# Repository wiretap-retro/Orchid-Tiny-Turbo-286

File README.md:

# Orchid Tiny Turbo 286
A clone of the Orchid Tiny Turbo 286 acclerator to upgrade an XT system. Based on schematics by Tube Time.

## Info / Warning
Build at your own risk This design is unconfirmed. PAL dumps have been added, courtesy of tomatolicious on the Retro Dreams and Techy Things Discord group. I do not have the original board, so this is a rough layout, not exactly the same size since it uses socketed footprints. However, it does abide by the ISA standard height (121.92mm) and uses a readily available slot cover that would need to be drilled for the switch to fit through. Board may require some more work -- this is considered a non-functional alpha release.
\
\
Built per the schematics from Tube Time's github found here: https://github.com/schlae/tiny-turbo-286

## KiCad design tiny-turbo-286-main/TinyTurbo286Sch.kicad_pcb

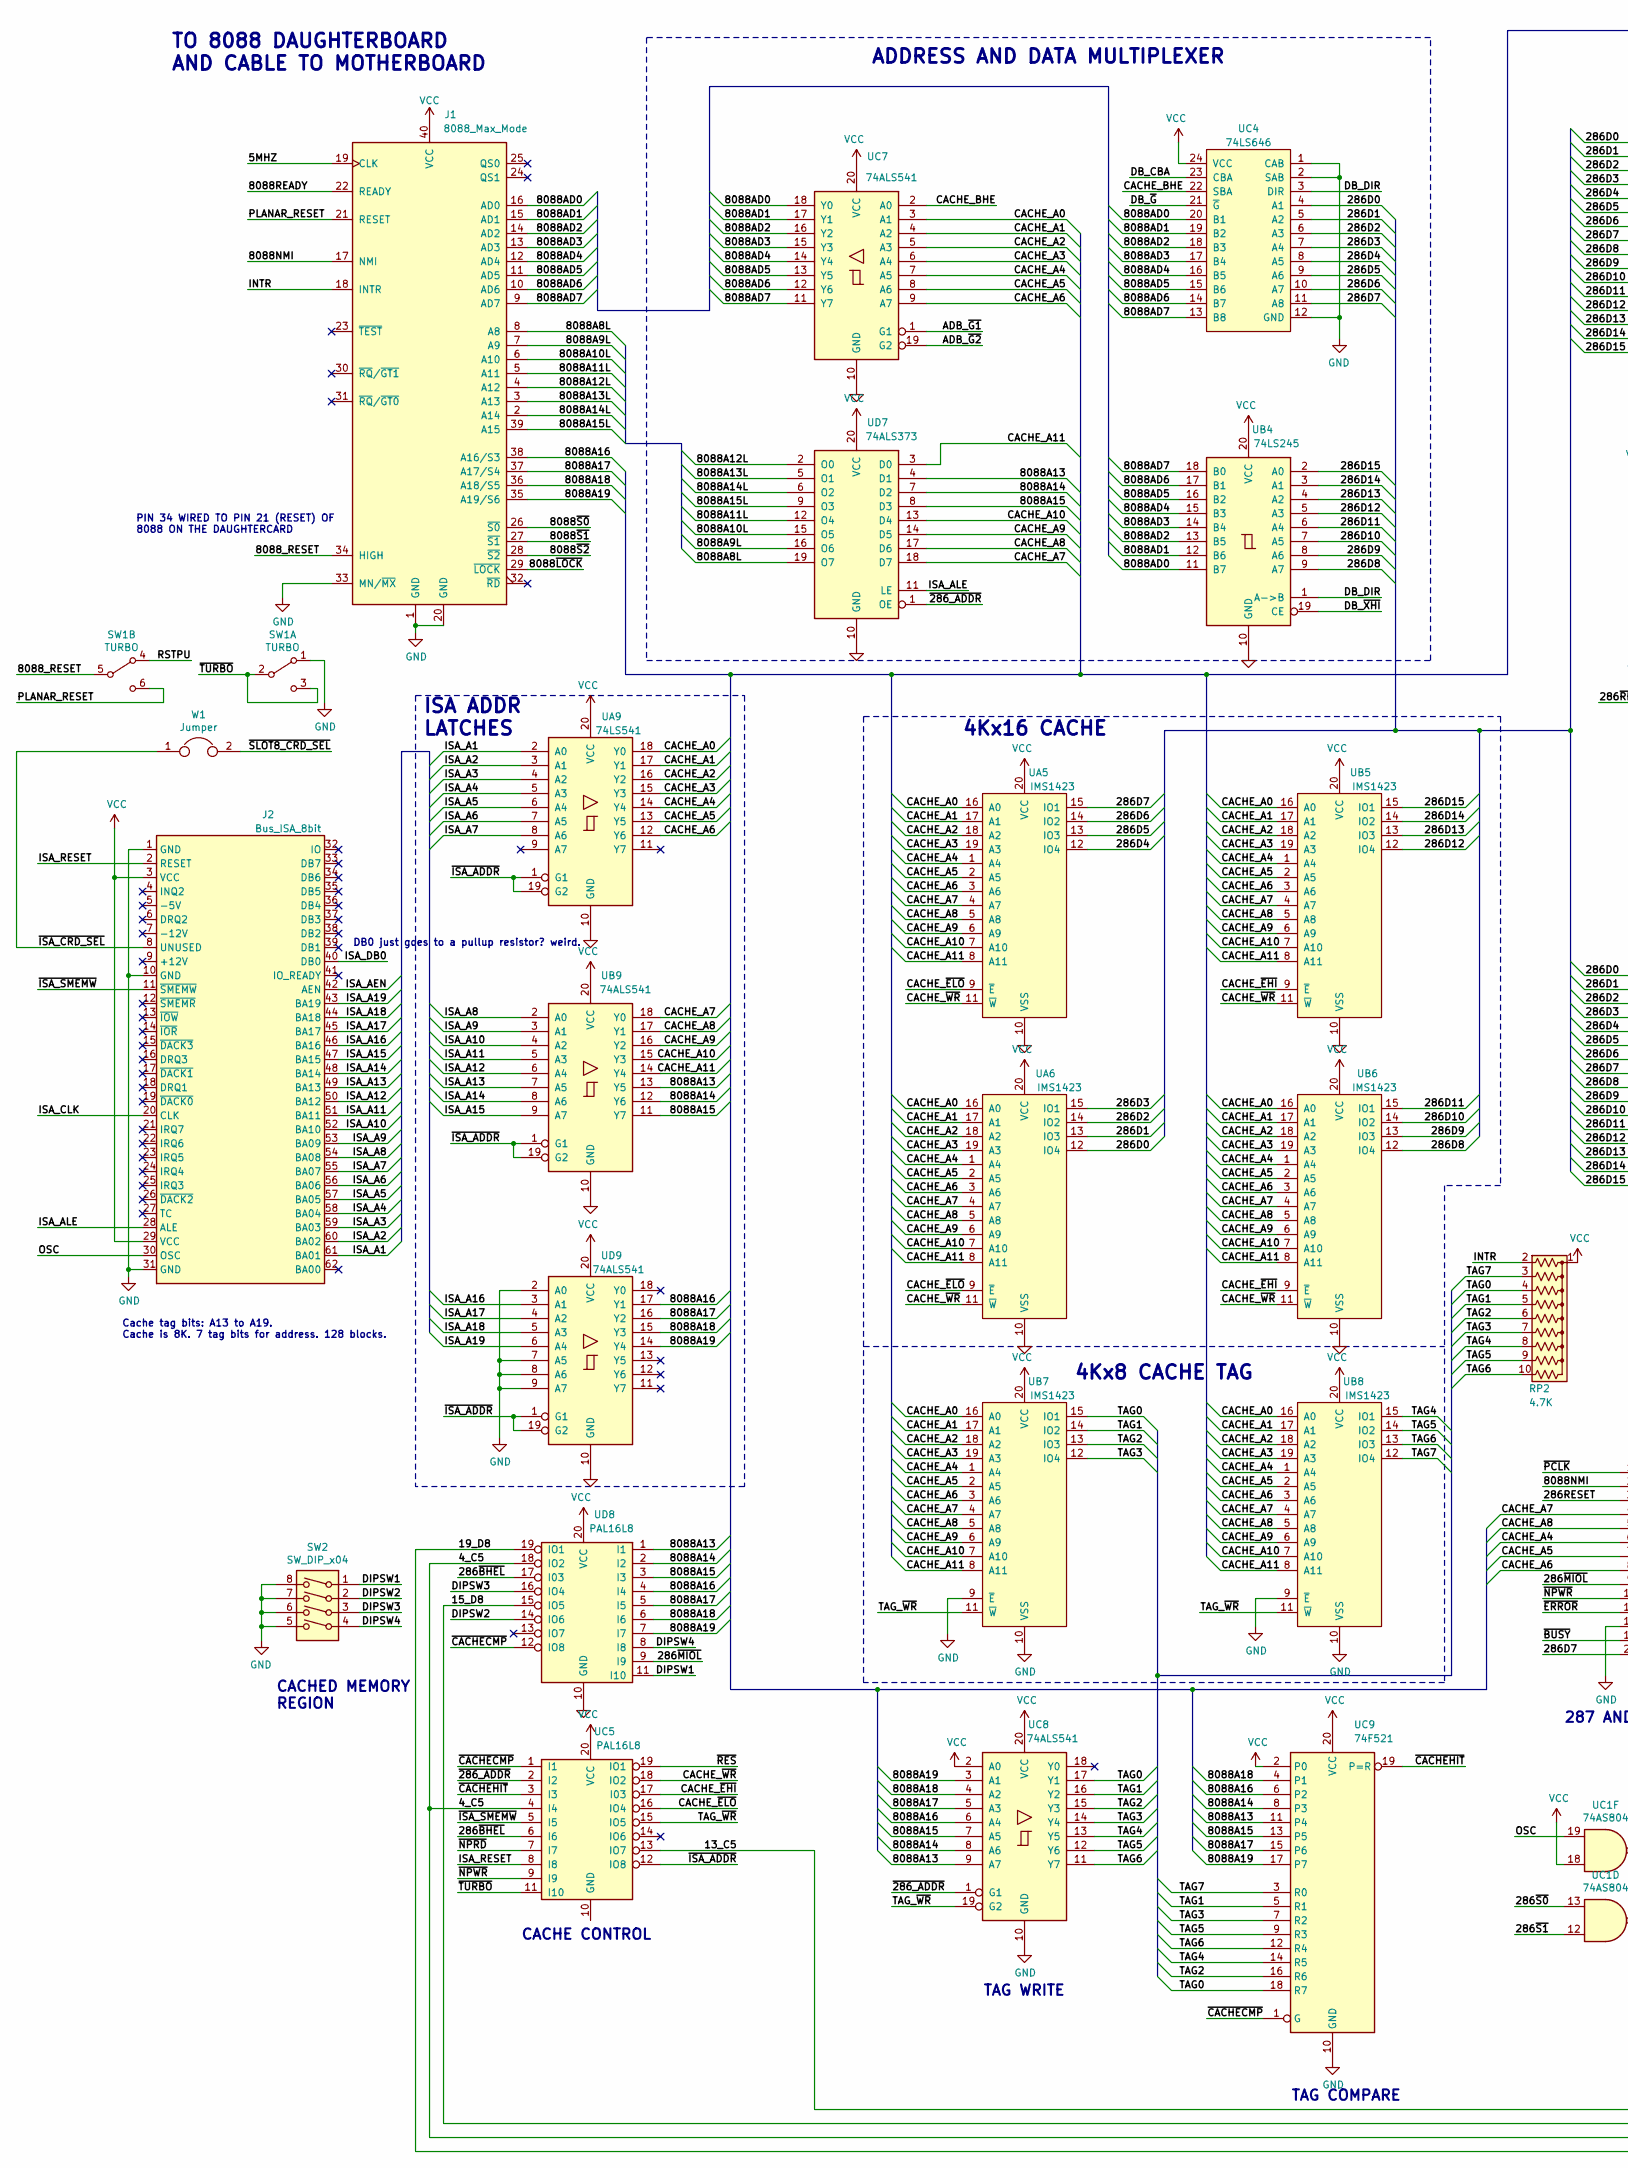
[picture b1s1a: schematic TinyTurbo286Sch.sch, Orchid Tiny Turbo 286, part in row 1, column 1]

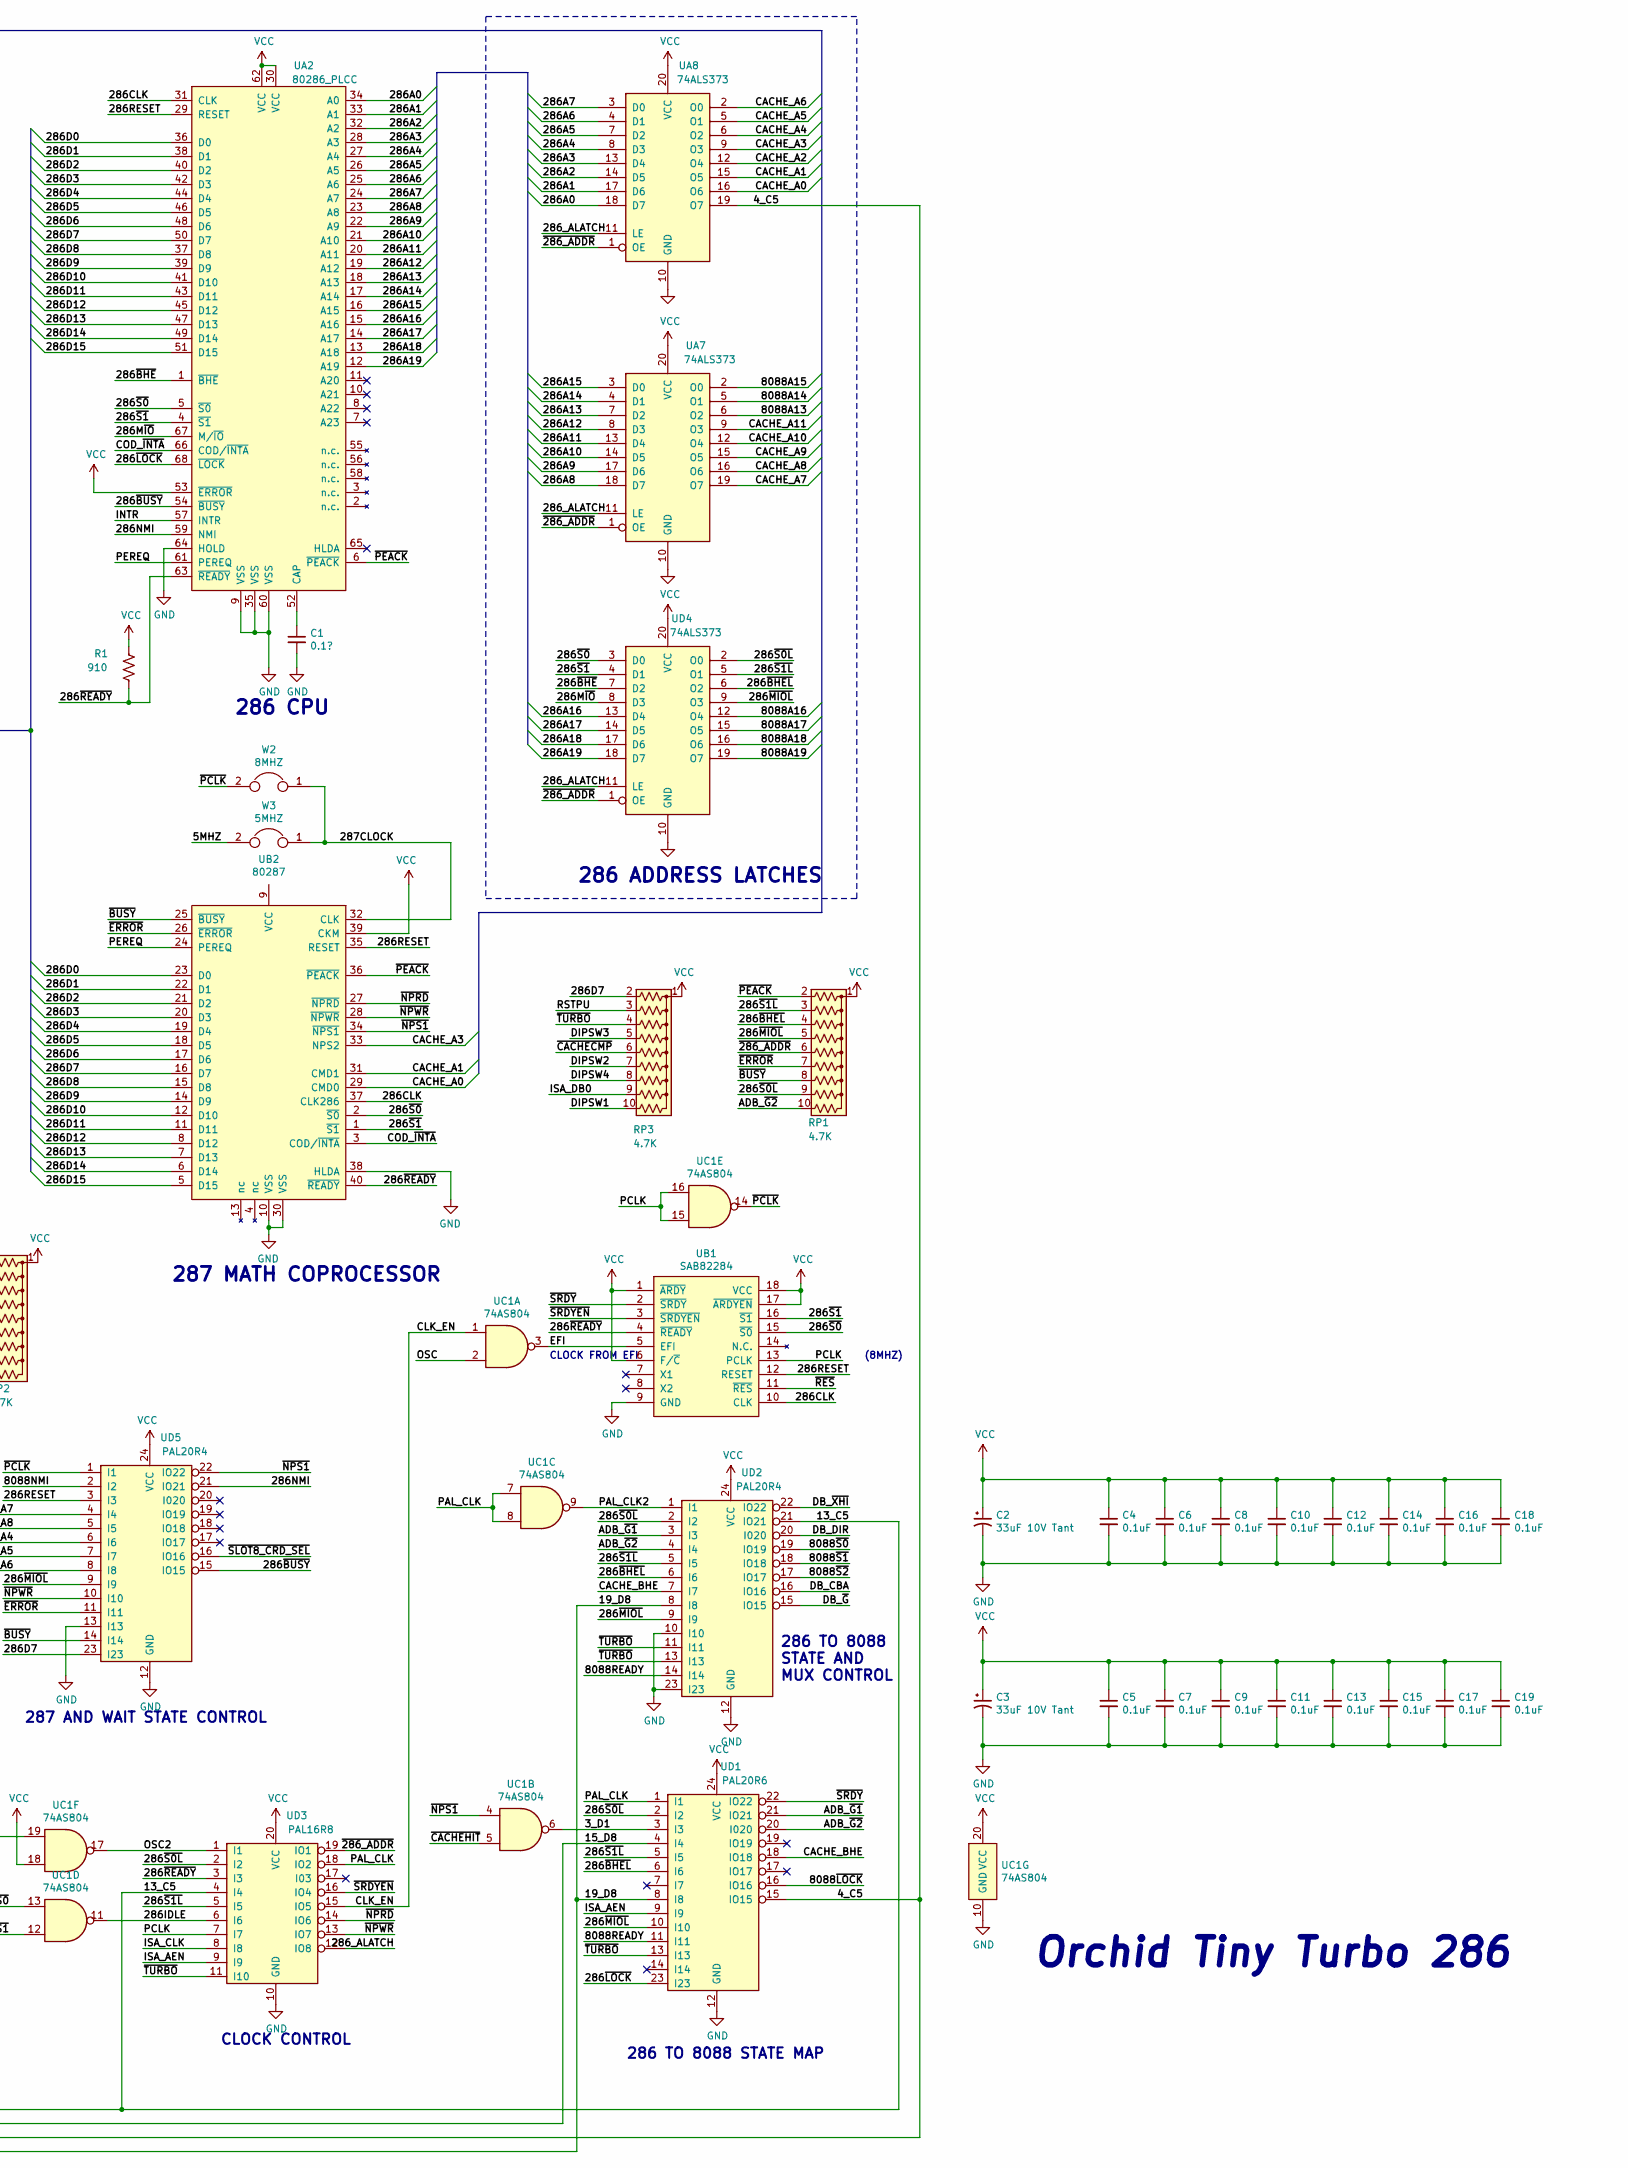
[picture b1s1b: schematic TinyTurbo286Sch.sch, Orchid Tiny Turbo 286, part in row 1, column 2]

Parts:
C1: 0.1?; C320C104J3G5TA
C2, C3: 33uF 10V Tant; CP_Radial_Tantal_D6.0mm_P5.00mm
C4, C5, C6, C7, C8, C9, C10, C11, C12, C13, C14, C15, C16, C17, C18, C19: 0.1uF; C320C104J3G5TA
J1: 8088_Max_Mode; PinSocket_2x20_P2.54mm_Vertical
J2: Bus_ISA_8bit; BUS_XT
R1: 910; R_Axial_DIN0207_L6.3mm_D2.5mm_P7.62mm_Horizontal
RP1, RP2, RP3: 4.7K; R_Array_SIP10
SW1: TURBO; A201MD9AQ04
SW2: SW_DIP_x04; DIP810W60P254L1209H480Q8N
UA2: 80286_PLCC; PLCC-68_THT-Socket
UA5, UA6: IMS1423; DIP-20_W7.62mm_Socket
UA7, UA8: 74ALS373; DIP-20_W7.62mm_Socket
UA9: 74LS541; DIP-20_W7.62mm_Socket
UB1: SAB82284; DIP-18_W7.62mm_Socket
UB2: 80287; DIP-40_W15.24mm_Socket
UB4: 74LS245; DIP-20_W7.62mm_Socket
UB5, UB6, UB7, UB8: IMS1423; DIP-20_W7.62mm_Socket
UB9: 74ALS541; DIP-20_W7.62mm_Socket
UC1: 74AS804; DIP-20_W7.62mm_Socket
UC4: 74LS646; DIP-24_W7.62mm_Socket
UC5: PAL16L8; DIP-20_W7.62mm_Socket
UC7, UC8: 74ALS541; DIP-20_W7.62mm_Socket
UC9: 74F521; DIP-20_W7.62mm_Socket
UD1: PAL20R6; DIP-24_W7.62mm_Socket
UD2, UD5: PAL20R4; DIP-24_W7.62mm_Socket
UD3: PAL16R8; DIP-20_W7.62mm_Socket
UD4, UD7: 74ALS373; DIP-20_W7.62mm_Socket
UD8: PAL16L8; DIP-20_W7.62mm_Socket
UD9: 74ALS541; DIP-20_W7.62mm_Socket
W1: Jumper; PinHeader_1x02_P2.54mm_Vertical
W2: 8MHZ; PinHeader_1x02_P2.54mm_Vertical
W3: 5MHZ; PinHeader_1x02_P2.54mm_Vertical

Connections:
/3_D1: UC1.6, UD1.3 (I3)
/4_C5: UA8.19 (O7), UC5.4 (I4), UD1.15 (IO15), UD8.18 (IO2)
/5MHZ: J1.19 (CLK), W3.2
/13_C5: UC5.13 (IO7), UD2.21 (IO21), UD3.4 (I4)
/15_D8: UD1.4 (I4), UD8.15 (IO5)
/19_D8: UD1.8 (I8), UD2.8 (I8), UD8.19 (IO1)
/286A0: UA2.34 (A0), UA8.18 (D7)
/286A1: UA2.33 (A1), UA8.17 (D6)
/286A2: UA2.32 (A2), UA8.14 (D5)
/286A3: UA2.28 (A3), UA8.13 (D4)
/286A4: UA2.27 (A4), UA8.8 (D3)
/286A5: UA2.26 (A5), UA8.7 (D2)
/286A6: UA2.25 (A6), UA8.4 (D1)
/286A7: UA2.24 (A7), UA8.3 (D0)
/286A8: UA2.23 (A8), UA7.18 (D7)
/286A9: UA2.22 (A9), UA7.17 (D6)
/286A10: UA2.21 (A10), UA7.14 (D5)
/286A11: UA2.20 (A11), UA7.13 (D4)
/286A12: UA2.19 (A12), UA7.8 (D3)
/286A13: UA2.18 (A13), UA7.7 (D2)
/286A14: UA2.17 (A14), UA7.4 (D1)
/286A15: UA2.16 (A15), UA7.3 (D0)
/286A16: UA2.15 (A16), UD4.13 (D4)
/286A17: UA2.14 (A17), UD4.14 (D5)
/286A18: UA2.13 (A18), UD4.17 (D6)
/286A19: UA2.12 (A19), UD4.18 (D7)
/286CLK: UA2.31 (CLK), UB1.10 (CLK), UB2.37 (CLK286)
/286D0: UA2.36 (D0), UA6.12 (IO4), UB2.23 (D0), UC4.4 (A1)
/286D1: UA2.38 (D1), UA6.13 (IO3), UB2.22 (D1), UC4.5 (A2)
/286D2: UA2.40 (D2), UA6.14 (IO2), UB2.21 (D2), UC4.6 (A3)
/286D3: UA2.42 (D3), UA6.15 (IO1), UB2.20 (D3), UC4.7 (A4)
/286D4: UA2.44 (D4), UA5.12 (IO4), UB2.19 (D4), UC4.8 (A5)
/286D5: UA2.46 (D5), UA5.13 (IO3), UB2.18 (D5), UC4.9 (A6)
/286D6: UA2.48 (D6), UA5.14 (IO2), UB2.17 (D6), UC4.10 (A7)
/286D7: RP3.2 (R1), UA2.50 (D7), UA5.15 (IO1), UB2.16 (D7), UC4.11 (A8), UD5.23 (I23)
/286D8: UA2.37 (D8), UB2.15 (D8), UB4.9 (A7), UB6.12 (IO4)
/286D9: UA2.39 (D9), UB2.14 (D9), UB4.8 (A6), UB6.13 (IO3)
/286D10: UA2.41 (D10), UB2.12 (D10), UB4.7 (A5), UB6.14 (IO2)
/286D11: UA2.43 (D11), UB2.11 (D11), UB4.6 (A4), UB6.15 (IO1)
/286D12: UA2.45 (D12), UB2.8 (D12), UB4.5 (A3), UB5.12 (IO4)
/286D13: UA2.47 (D13), UB2.7 (D13), UB4.4 (A2), UB5.13 (IO3)
/286D14: UA2.49 (D14), UB2.6 (D14), UB4.3 (A1), UB5.14 (IO2)
/286D15: UA2.51 (D15), UB2.5 (D15), UB4.2 (A0), UB5.15 (IO1)
/286IDLE: UC1.11, UD3.6 (I6)
/286M~IO: UA2.67 (M/~IO), UD4.8 (D3)
/286NMI: UA2.59 (NMI), UD5.21 (IO21)
/286RESET: UA2.29 (RESET), UB1.12 (RESET), UB2.35 (RESET), UD5.3 (I3)
/286_ALATCH: UA7.11 (LE), UA8.11 (LE), UD3.12 (IO8), UD4.11 (LE)
/286~BHE: UA2.1 (~BHE), UD4.7 (D2)
/286~BHEL: RP1.4 (R3), UC5.6 (I6), UD1.6 (I6), UD2.6 (I6), UD4.6 (O2), UD8.17 (I03)
/286~BUSY: UA2.54 (~BUSY), UD5.15 (IO15)
/286~LOCK: UA2.68 (~LOCK), UD1.23 (I23)
/286~MIOL: RP1.5 (R4), UD1.10 (I10), UD2.9 (I9), UD4.9 (O3), UD5.9 (I9), UD8.9 (I9)
/286~READY: R1.2, UA2.63 (~READY), UB1.4 (~READY), UB2.40 (~READY), UD3.3 (I3)
/286~S0: UA2.5 (~S0), UB1.15 (~S0), UB2.2 (~S0), UC1.13, UD4.3 (D0)
/286~S0L: RP1.9 (R8), UD1.2 (I2), UD2.2 (I2), UD3.2 (I2), UD4.2 (O0)
/286~S1: UA2.4 (~S1), UB1.16 (~S1), UB2.1 (~S1), UC1.12, UD4.4 (D1)
/286~S1L: RP1.3 (R2), UD1.5 (I5), UD2.5 (I5), UD3.5 (I5), UD4.5 (O1)
/287CLOCK: UB2.32 (CLK), W2.1, W3.1
/8088A8L: J1.8 (A8), UD7.19 (O7)
/8088A9L: J1.7 (A9), UD7.16 (O6)
/8088A10L: J1.6 (A10), UD7.15 (O5)
/8088A11L: J1.5 (A11), UD7.12 (O4)
/8088A12L: J1.4 (A12), UD7.2 (O0)
/8088A13: UA7.6 (O2), UB9.13 (Y5), UC8.9 (A7), UC9.11 (P4), UD7.4 (D1), UD8.1 (I1)
/8088A13L: J1.3 (A13), UD7.5 (O1)
/8088A14: UA7.5 (O1), UB9.12 (Y6), UC8.8 (A6), UC9.8 (P3), UD7.7 (D2), UD8.2 (I2)
/8088A14L: J1.2 (A14), UD7.6 (O2)
/8088A15: UA7.2 (O0), UB9.11 (Y7), UC8.7 (A5), UC9.13 (P5), UD7.8 (D3), UD8.3 (I3)
/8088A15L: J1.39 (A15), UD7.9 (O3)
/8088A16: J1.38 (A16/S3), UC8.6 (A4), UC9.6 (P2), UD4.12 (O4), UD8.4 (I4), UD9.17 (Y1)
/8088A17: J1.37 (A17/S4), UC8.5 (A3), UC9.15 (P6), UD4.15 (O5), UD8.5 (I5), UD9.16 (Y2)
/8088A18: J1.36 (A18/S5), UC8.4 (A2), UC9.4 (P1), UD4.16 (O6), UD8.6 (I6), UD9.15 (Y3)
/8088A19: J1.35 (A19/S6), UC8.3 (A1), UC9.17 (P7), UD4.19 (O7), UD8.7 (I7), UD9.14 (Y4)
/8088AD0: J1.16 (AD0), UB4.11 (B7), UC4.20 (B1), UC7.18 (Y0)
/8088AD1: J1.15 (AD1), UB4.12 (B6), UC4.19 (B2), UC7.17 (Y1)
/8088AD2: J1.14 (AD2), UB4.13 (B5), UC4.18 (B3), UC7.16 (Y2)
/8088AD3: J1.13 (AD3), UB4.14 (B4), UC4.17 (B4), UC7.15 (Y3)
/8088AD4: J1.12 (AD4), UB4.15 (B3), UC4.16 (B5), UC7.14 (Y4)
/8088AD5: J1.11 (AD5), UB4.16 (B2), UC4.15 (B6), UC7.13 (Y5)
/8088AD6: J1.10 (AD6), UB4.17 (B1), UC4.14 (B7), UC7.12 (Y6)
/8088AD7: J1.9 (AD7), UB4.18 (B0), UC4.13 (B8), UC7.11 (Y7)
/8088NMI: J1.17 (NMI), UD5.2 (I2)
/8088READY: J1.22 (READY), UD1.11 (I11), UD2.14 (I14)
/8088_RESET: J1.34 (HIGH), SW1.5 (B)
/8088~LOCK: J1.29 (~LOCK~), UD1.16 (IO16)
/8088~S0: J1.26 (~S0~), UD2.19 (IO19)
/8088~S1: J1.27 (~S1~), UD2.18 (IO18)
/8088~S2: J1.28 (~S2~), UD2.17 (IO17)
/ADB_~G1: UC7.1 (G1), UD1.21 (IO21), UD2.3 (I3)
/ADB_~G2: RP1.10 (R9), UC7.19 (G2), UD1.20 (I020), UD2.4 (I4)
/CACHE_A0: UA5.16 (A0), UA6.16 (A0), UA8.16 (O6), UA9.18 (Y0), UB2.29 (CMD0), UB5.16 (A0), UB6.16 (A0), UB7.16 (A0), UB8.16 (A0), UC7.3 (A1)
/CACHE_A1: UA5.17 (A1), UA6.17 (A1), UA8.15 (O5), UA9.17 (Y1), UB2.31 (CMD1), UB5.17 (A1), UB6.17 (A1), UB7.17 (A1), UB8.17 (A1), UC7.4 (A2)
/CACHE_A2: UA5.18 (A2), UA6.18 (A2), UA8.12 (O4), UA9.16 (Y2), UB5.18 (A2), UB6.18 (A2), UB7.18 (A2), UB8.18 (A2), UC7.5 (A3)
/CACHE_A3: UA5.19 (A3), UA6.19 (A3), UA8.9 (O3), UA9.15 (Y3), UB2.33 (NPS2), UB5.19 (A3), UB6.19 (A3), UB7.19 (A3), UB8.19 (A3), UC7.6 (A4)
/CACHE_A4: UA5.1 (A4), UA6.1 (A4), UA8.6 (O2), UA9.14 (Y4), UB5.1 (A4), UB6.1 (A4), UB7.1 (A4), UB8.1 (A4), UC7.7 (A5), UD5.6 (I6)
/CACHE_A5: UA5.2 (A5), UA6.2 (A5), UA8.5 (O1), UA9.13 (Y5), UB5.2 (A5), UB6.2 (A5), UB7.2 (A5), UB8.2 (A5), UC7.8 (A6), UD5.7 (I7)
/CACHE_A6: UA5.3 (A6), UA6.3 (A6), UA8.2 (O0), UA9.12 (Y6), UB5.3 (A6), UB6.3 (A6), UB7.3 (A6), UB8.3 (A6), UC7.9 (A7), UD5.8 (I8)
/CACHE_A7: UA5.4 (A7), UA6.4 (A7), UA7.19 (O7), UB5.4 (A7), UB6.4 (A7), UB7.4 (A7), UB8.4 (A7), UB9.18 (Y0), UD5.4 (I4), UD7.18 (D7)
/CACHE_A8: UA5.5 (A8), UA6.5 (A8), UA7.16 (O6), UB5.5 (A8), UB6.5 (A8), UB7.5 (A8), UB8.5 (A8), UB9.17 (Y1), UD5.5 (I5), UD7.17 (D6)
/CACHE_A9: UA5.6 (A9), UA6.6 (A9), UA7.15 (O5), UB5.6 (A9), UB6.6 (A9), UB7.6 (A9), UB8.6 (A9), UB9.16 (Y2), UD7.14 (D5)
/CACHE_A10: UA5.7 (A10), UA6.7 (A10), UA7.12 (O4), UB5.7 (A10), UB6.7 (A10), UB7.7 (A10), UB8.7 (A10), UB9.15 (Y3), UD7.13 (D4)
/CACHE_A11: UA5.8 (A11), UA6.8 (A11), UA7.9 (O3), UB5.8 (A11), UB6.8 (A11), UB7.8 (A11), UB8.8 (A11), UB9.14 (Y4), UD7.3 (D0)
/CACHE_BHE: UC4.22 (SBA), UC7.2 (A0), UD1.18 (IO18), UD2.7 (I7)
/CACHE_~EHI: UB5.9 (~E), UB6.9 (~E), UC5.17 (I03)
/CACHE_~ELO: UA5.9 (~E), UA6.9 (~E), UC5.16 (IO4)
/CACHE_~WR: UA5.11 (~W), UA6.11 (~W), UB5.11 (~W), UB6.11 (~W), UC5.18 (IO2)
/CLK_EN: UC1.1, UD3.15 (IO5)
/COD_~INTA: UA2.66 (COD/~INTA), UB2.3 (COD/~INTA)
/DB_CBA: UC4.23 (CBA), UD2.16 (IO16)
/DB_DIR: UB4.1 (A->B), UC4.3 (DIR), UD2.20 (I020)
/DB_~G: UC4.21 (~G), UD2.15 (IO15)
/DB_~XHI: UB4.19 (CE), UD2.22 (IO22)
/DIPSW1: RP3.10 (R9), SW2.1, UD8.11 (I10)
/DIPSW2: RP3.7 (R6), SW2.2, UD8.14 (IO6)
/DIPSW3: RP3.5 (R4), SW2.3, UD8.16 (IO4)
/DIPSW4: RP3.8 (R7), SW2.4, UD8.8 (I8)
/EFI: UB1.5 (EFI), UC1.3
/INTR: J1.18 (INTR), RP2.2 (R1), UA2.57 (INTR)
/ISA_A1: J2.61 (BA01), UA9.2 (A0)
/ISA_A2: J2.60 (BA02), UA9.3 (A1)
/ISA_A3: J2.59 (BA03), UA9.4 (A2)
/ISA_A4: J2.58 (BA04), UA9.5 (A3)
/ISA_A5: J2.57 (BA05), UA9.6 (A4)
/ISA_A6: J2.56 (BA06), UA9.7 (A5)
/ISA_A7: J2.55 (BA07), UA9.8 (A6)
/ISA_A8: J2.54 (BA08), UB9.2 (A0)
/ISA_A9: J2.53 (BA09), UB9.3 (A1)
/ISA_A10: J2.52 (BA10), UB9.4 (A2)
/ISA_A11: J2.51 (BA11), UB9.5 (A3)
/ISA_A12: J2.50 (BA12), UB9.6 (A4)
/ISA_A13: J2.49 (BA13), UB9.7 (A5)
/ISA_A14: J2.48 (BA14), UB9.8 (A6)
/ISA_A15: J2.47 (BA15), UB9.9 (A7)
/ISA_A16: J2.46 (BA16), UD9.3 (A1)
/ISA_A17: J2.45 (BA17), UD9.4 (A2)
/ISA_A18: J2.44 (BA18), UD9.5 (A3)
/ISA_A19: J2.43 (BA19), UD9.6 (A4)
/ISA_AEN: J2.42 (AEN), UD1.9 (I9), UD3.9 (I9)
/ISA_ALE: J2.28 (ALE), UD7.11 (LE)
/ISA_CLK: J2.20 (CLK), UD3.8 (I8)
/ISA_DB0: J2.40 (DB0), RP3.9 (R8)
/ISA_RESET: J2.2 (RESET), UC5.8 (I8)
/OSC: J2.30 (OSC), UC1.2, UC1.19
/OSC2: UC1.17, UD3.1 (I1)
/PAL_CLK: UC1.7, UC1.8, UD1.1 (I1), UD3.18 (IO2)
/PAL_CLK2: UC1.9, UD2.1 (I1)
/PCLK: UB1.13 (PCLK), UC1.15, UC1.16, UD3.7 (I7)
/PEREQ: UA2.61 (PEREQ), UB2.24 (PEREQ)
/PLANAR_RESET: J1.21 (RESET), SW1.6 (C)
/RSTPU: RP3.3 (R2), SW1.4 (A)
/TAG0: RP2.4 (R3), UB7.15 (IO1), UC8.17 (Y1), UC9.18 (R7)
/TAG1: RP2.5 (R4), UB7.14 (IO2), UC8.16 (Y2), UC9.5 (R1)
/TAG2: RP2.6 (R5), UB7.13 (IO3), UC8.15 (Y3), UC9.16 (R6)
/TAG3: RP2.7 (R6), UB7.12 (IO4), UC8.14 (Y4), UC9.7 (R2)
/TAG4: RP2.8 (R7), UB8.15 (IO1), UC8.13 (Y5), UC9.14 (R5)
/TAG5: RP2.9 (R8), UB8.14 (IO2), UC8.12 (Y6), UC9.9 (R3)
/TAG6: RP2.10 (R9), UB8.13 (IO3), UC8.11 (Y7), UC9.12 (R4)
/TAG7: RP2.3 (R2), UB8.12 (IO4), UC9.3 (R0)
/TAG_~WR: UB7.11 (~W), UB8.11 (~W), UC5.15 (IO5), UC8.19 (G2)
/~286_ADDR: RP1.6 (R5), UA7.1 (OE), UA8.1 (OE), UC5.2 (I2), UC8.1 (G1), UD3.19 (IO1), UD4.1 (OE), UD7.1 (OE)
/~BUSY: RP1.8 (R7), UB2.25 (~BUSY), UD5.14 (I14)
/~CACHECMP: RP3.6 (R5), UC5.1 (I1), UC9.1 (G), UD8.12 (IO8)
/~CACHEHIT: UC1.5, UC5.3 (I3), UC9.19 (P=R)
/~ERROR: RP1.7 (R6), UB2.26 (~ERROR), UD5.11 (I11)
/~ISA_ADDR: UA9.1 (G1), UA9.19 (G2), UB9.1 (G1), UB9.19 (G2), UC5.12 (IO8), UD9.1 (G1), UD9.19 (G2)
/~ISA_CRD_SEL: J2.8 (UNUSED), W1.1
/~ISA_SMEMW: J2.11 (~SMEMW), UC5.5 (I5)
/~NPRD: UB2.27 (~NPRD), UC5.7 (I7), UD3.14 (IO6)
/~NPS1: UB2.34 (~NPS1), UC1.4, UD5.22 (IO22)
/~NPWR: UB2.28 (~NPWR), UC5.9 (I9), UD3.13 (IO7), UD5.10 (I10)
/~PCLK: UC1.14, UD5.1 (I1), W2.2
/~PEACK: RP1.2 (R1), UA2.6 (~PEACK), UB2.36 (~PEACK)
/~RES: UB1.11 (~RES), UC5.19 (IO1)
/~SLOT8_CRD_SEL: UD5.16 (IO16), W1.2
/~SRDY: UB1.2 (~SRDY), UD1.22 (IO22)
/~SRDYEN: UB1.3 (~SRDYEN), UD3.16 (IO4)
/~TURBO: RP3.4 (R3), SW1.2 (B), SW1.3 (C), UC5.11 (I10), UD1.13 (I13), UD2.11 (I11), UD2.13 (I13), UD3.11 (I10)
GND: C1.2, C2.2, C3.2, C4.2, C5.2, C6.2, C7.2, C8.2, C9.2, C10.2, C11.2, C12.2, C13.2, C14.2, C15.2, C16.2, C17.2, C18.2, C19.2, J1.1 (GND), J1.20 (GND), J1.33 (MN/~MX~), J2.1 (GND), J2.10 (GND), J2.31 (GND), SW1.1 (A), SW2.5, SW2.6, SW2.7, SW2.8, UA2.9 (VSS), UA2.35 (VSS), UA2.60 (VSS), UA2.64 (HOLD), UA5.10 (VSS), UA6.10 (VSS), UA7.10 (GND), UA8.10 (GND), UA9.10 (GND), UB1.9 (GND), UB2.10 (VSS), UB2.30 (VSS), UB2.38 (HLDA), UB4.10 (GND), UB5.10 (VSS), UB6.10 (VSS), UB7.9 (~E), UB7.10 (VSS), UB8.9 (~E), UB8.10 (VSS), UB9.10 (GND), UC1.10 (GND), UC4.1 (CAB), UC4.2 (SAB), UC4.12 (GND), UC7.10 (GND), UC8.10 (GND), UC9.10 (GND), UD1.12 (GND), UD2.10 (I10), UD2.12 (GND), UD2.23 (I23), UD3.10 (GND), UD4.10 (GND), UD5.12 (GND), UD5.13 (I13), UD7.10 (GND), UD8.10 (GND), UD9.2 (A0), UD9.7 (A5), UD9.8 (A6), UD9.9 (A7), UD9.10 (GND)
unnamed: C1.1, UA2.52 (CAP)
VCC: C2.1, C3.1, C4.1, C5.1, C6.1, C7.1, C8.1, C9.1, C10.1, C11.1, C12.1, C13.1, C14.1, C15.1, C16.1, C17.1, C18.1, C19.1, J1.40 (VCC), J2.3 (VCC), J2.29 (VCC), R1.1, RP1.1 (common), RP2.1 (common), RP3.1 (common), UA2.30 (VCC), UA2.53 (~ERROR), UA2.62 (VCC), UA5.20 (VCC), UA6.20 (VCC), UA7.20 (VCC), UA8.20 (VCC), UA9.20 (VCC), UB1.1 (~ARDY), UB1.6 (F/~C), UB1.17 (~ARDYEN), UB1.18 (VCC), UB2.39 (CKM), UB4.20 (VCC), UB5.20 (VCC), UB6.20 (VCC), UB7.20 (VCC), UB8.20 (VCC), UB9.20 (VCC), UC1.18, UC1.20 (VCC), UC4.24 (VCC), UC5.20 (VCC), UC7.20 (VCC), UC8.2 (A0), UC8.20 (VCC), UC9.2 (P0), UC9.20 (VCC), UD1.24 (VCC), UD2.24 (VCC), UD3.20 (VCC), UD4.20 (VCC), UD5.24 (VCC), UD7.20 (VCC), UD8.20 (VCC), UD9.20 (VCC)

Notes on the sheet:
Cache tag bits: A13 to A19. Cache is 8K. 7 tag bits for address. 128 blocks.
PIN 34 WIRED TO PIN 21 (RESET) OF 8088 ON THE DAUGHTERCARD
CLOCK FROM EFI
DB0 just goes to a pullup resistor? weird.
CACHE CONTROL
287 AND WAIT STATE CONTROL
CLOCK CONTROL
286 TO 8088 STATE AND MUX CONTROL
286 TO 8088 STATE MAP
CACHED MEMORY REGION
TAG WRITE
TAG COMPARE
287 MATH COPROCESSOR
286 CPU
286 ADDRESS LATCHES
(8MHZ)
4Kx8 CACHE TAG
4Kx16 CACHE
ADDRESS AND DATA MULTIPLEXER
ISA ADDR LATCHES
TO 8088 DAUGHTERBOARD AND CABLE TO MOTHERBOARD
Orchid Tiny Turbo 286

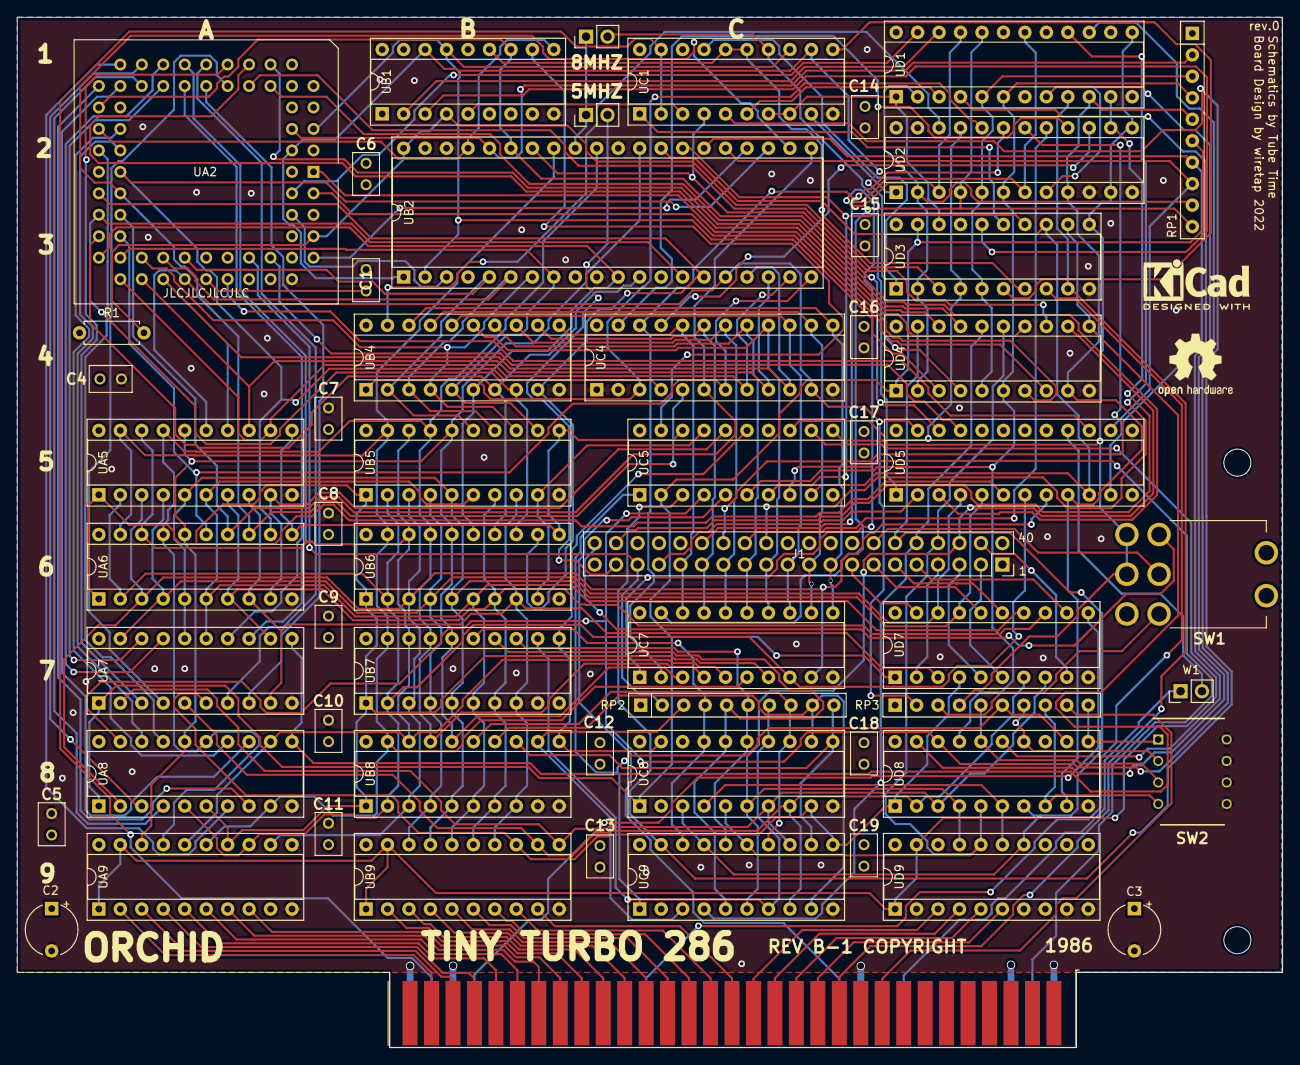
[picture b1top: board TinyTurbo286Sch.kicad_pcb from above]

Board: 4 copper layers, 149.7 x 121.9 mm, 60 parts (0 on the bottom side), 181 nets.

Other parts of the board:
P6, P7: CONN_1; MountingHole_3.2mm_M3

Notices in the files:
tiny-turbo-286-main/TinyTurbo286Sch.sch:
(C) 2021
This work is licensed under a Creative Commons
